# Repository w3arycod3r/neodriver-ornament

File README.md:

# neodriver-ornament
# Demo

# Goal
Create a rechargeable, battery-powered Christmas ornament using Adafruit's ["NeoPixels"](https://www.adafruit.com/category/168) (WS2812B RGB addressable LEDs). The ornament should contain a hole for a ribbon to hang on a tree. The ornament should be "small enough" as to not look out of place on a tree. It should be balanced and as symmetrical as possible so that it will hang straight. The weight should be comparable to other common ornaments. The battery should last for several days/weeks of continuous use.

Animations should be colorful, interesting, and eye-catching. It is acceptable to have a low duty cycle, i.e. the LEDs can have a short ON time playing an animation followed by a longer OFF time to save power. 
# Hardware
For the LEDs, I found various carrier boards of the [WS2812B](docs/WS2812B/WS2812B.pdf) RGB LEDs on eBay. I found square matrices, rings, and circles of various sizes. Search for "WS2812B Ring" or "WS2812B 5X5". Most of these boards simply had the LEDs soldered on one side with appropriate decoupling caps and traces connecting them all in a chain. The important connections (VDD, DIN, & GND) were exposed on the other side, to surface mount pads. I used small stranded wires from ribbon cables to fashion my own cables and connectors for each board. I soldered the wires to the pads, providing some strain relief with hot glue, then crimped a 3P JST-XH female connector to the other end. I would use a male 3P JST-XH on my driver board and connect the LED boards using this interface. This would make it easy to switch out and test different LED boards. Making these connectors was tedious and the solder connections are quite fragile.

I chose the [ATtiny85](https://www.microchip.com/en-us/product/ATTINY85) for the microcontroller, as it is small, inexpensive, has various low-power modes, is available in a DIP-8 package, has sufficient I/O, and has some Arduino IDE support with extensions. I wanted all my components to be through-hole for easy assembly. I planned to have a potentiometer for brightness control, two pushbuttons for changing animations, and a power switch.

Later, I would discover that the NeoPixels drew several milliamps of current, even when they were switched OFF (commanded to show RGB = 0,0,0). So, I picked a nMOS power transistor to switch the GND of the NeoPixels using the microcontroller. I also switched the GND on the pot to save additional power. 

For the battery, I found a neat module which combines a LiFePO4 cell, holder, and USB charge circuit into a single, easy to solder PCB:

https://www.tindie.com/products/silicognition/lifepo4weredusb/  

I wanted to be able to reprogram the microcontroller after the device was assembled, so I included a AVR-ISP header on the board. Not quite as convenient as the USB connector on an Arduino, but good enough for my purposes. This means that I will need a AVR-ISP programmer. I used the official [Atmel-ICE](https://www.microchip.com/en-us/development-tool/ATATMEL-ICE) programmer. I looked into some of the third-party programmers, but I wasn't happy with the way they handled powering the board. The Atmel-ICE does not power the board but instead samples the VDD line and converts the 5V USB programming signals to the voltage level your board uses.

# Schematic

A few notes about the schematic: 
1. I added a jumper in series with the battery positive terminal so I could easily measure power consumption of the entire circuit. This was very useful later during my power optimization efforts.
2. C1 is a decoupling cap for the micro, which will be placed close to the power pins during layout.
3. The micro is at the heart of the circuit, reading the switches and pot inputs, driving the single data line for the NeoPixels, and controlling the nMOS power transistor. Internal pull-ups are used for the switches.
4. R2 is in series with the NeoPixel DIN, based on advice from Adafruit. In theory, this resistor reduces the reflections (sharp over-voltage peaks) on this high-speed digital data line.
5. The I/O lines are shared with the programming lines, with isolation resistors where necessary (R3). There is a pull-up (R1) on the reset line, so that the micro is only reset when the programmer brings the line low.
6. R5 and C3 form a low-pass filter on the analog pot line, to remove any noise which may be on this line. The ADC inside the micro is configured to sample this pin.
7. R4 is a pull-down resistor so that the nMOS is OFF by default. The micro will bring the gate of the nMOS high in order to turn on the transistor and allow the NeoPixels to be powered.
8. There is a bulk cap (C2) close to the NeoPixel connector to buffer the power for the LEDs. These LEDs switch ON and OFF quickly and they require large spikes of current from the power rail. The cap will provide this current while smoothing out the voltage.
9. I picked the IRLU8743PBF for Q1 based on the convenient through-hole package (I-PAK), low ON resistance (~3.1 mOhms), small size, and low threshold voltage (~1.9V). However, it is a bit pricy. Others could certainly work in its place.

# PCB Design
## Breadboard & Protoboard
First, I soldered together a prototype on a piece of protoboard, based on my initial schematic. I also created a breadboard version for easy experimentation.

This wasn't very attractive, and it didn't hang very well on the tree, so I sought out to design a custom PCB. This was my first PCB design, so I learned a lot along the way. I decided to use KiCad, since it is FOSS and very beginner friendly. I watched and followed along with Digi-Key's [YouTube tutorial](https://www.youtube.com/playlist?list=PLEBQazB0HUyR24ckSZ5u05TZHV9khgA1O) on KiCad. Should you want to get a batch of these boards fabbed, you can find the [gerbers](kicad/export/gerbers) in the repo.

## v01
The layout for v01 of the PCB design was heavily based on the protoboard layout, for simplicity. I used [JLCPCB](https://jlcpcb.com/) to get the boards manufactured.  

## v02
For v02, I made several improvements:
1. Use a circular shape for smaller overall footprint and hopefully better balance on the tree
2. Place the battery (heaviest component) for better balance.
3. Replace the straight ISP header with a right angle one so that the port can be accessed even when the LEDs are hot-glued in place.
4. Add the nMOS transistor to switch the NeoPixel GND when in a low-power state.
5. Add a single hole at the top to attach a ribbon for hanging purposes.
6. Add rubber feet on bottom so the board can sit on a table without scratching the table or shorting connections.
7. Add some festive PCB art on the back! :D  

I discovered that the potentiometer was burning some power as well. Since I didn't need to read the value of the pot while in a low-power state, I decided to switch the GND of the pot using the same nMOS for the NeoPixels. I cut the GND connection on the pot and added a bodge wire to fix this, shown below:

## v03
For v03, I made a few minor improvements:
1. Rewire the pot so that the GND is switched along with the NeoPixel GND.
2. Rotate some components 45 degrees so that they are easier to access when the LEDs are fixed on top.
3. Add RC low-pass filter on the analog pot line, to filter out switching noise from NeoPixel data signal.
4. Enlarge pads on battery terminals for better connection

# Software
The main app [neo_driver_app.cpp](microchip-studio/neo_driver_app/neo_driver_app.cpp) has several important functions:
1. Process HMI inputs (left, right switches and potentiometer). The switches can scroll through all the animations and the pot can adjust the brightness of the LEDs.
2. LED adjustment mode: Holding one of the switches will cause the device to enter a LED adjustment mode. In this mode, pressing the left or right switches will decrement or increment the number of LEDs controlled by the device. This allows different sizes of matrices or rings to be used. Holding one of the switches again will save your adjustment into EEPROM memory, so that it is retained between power cycles.
3. Shuffle mode: Play the defined animations in a random sequence, without user intervention. After playing an animation, enter a low-power mode with micro in deep sleep, LEDs and pot OFF. The sleep time is variable, depending on the length of the last played animation. Wakeup from sleep is achieved using the watchdog timer. Also, pressing one of the switches will wake the device as well.
4. Battery management: Monitor for a low battery condition by measuring VDD on the micro and checking it against a set threshold. When this condition occurs, a flashing red "low battery" icon is shown for a few seconds and the device enters the low-power mode without the watchdog timer set. Therefore, the device will remain in low-power mode until it is woken with a switch or a power cycle. If the battery is still low, the device will repeat the "low battery" animation and return to the low-power mode. The device will be "locked out" until the battery voltage rises to a reasonable level (as a result of the user charging the battery).

I wrote the code with modularity in mind, so that it would be easy to add or remove animations. Also most parameters are pulled out into constants or data structures, so they can be easily tweaked.

## Animations
### Scrolling Text
In the EEPROM, I had space for 85 ASCII characters in a 5x5 bitmap font. The top 3 bits of each byte were unused. Most notably, I covered all the digits, capital letters, and some punctuation marks and symbols. In the program memory (flash), I store a few message strings in ASCII. This animation can select one of the messages and scroll it across the matrix in one color or in a flowing "rainbow" color effect.

Rendering a 5x5 framebuffer containing a character onto the 5x5 matrix was tricky because the LEDs are indexed sequentially, in a zig-zag pattern chosen for convenient routing on the matrix PCB. Below is an illustration of the index problem, with my choice for numbering rows and columns:

I came up with the following conversion equations for (row,col) to pixel index, depending on the orientation of the matrix (which determines location of first pixel and the pattern direction):
```C++
// Calculate pixel index from (row,col)
    #if   ANIM_ROT_SEL == 1
        if (u8_col % 2 == 0) { u8_pixIndex = u8_col*5     + 4-u8_row; }
        else                 { u8_pixIndex = u8_col*5     +   u8_row; }
    #elif ANIM_ROT_SEL == 2
        if (u8_row % 2 == 0) { u8_pixIndex = (4-u8_row)*5 + 4-u8_col; }
        else                 { u8_pixIndex = (4-u8_row)*5 +   u8_col; }
    #elif ANIM_ROT_SEL == 3
        if (u8_col % 2 == 0) { u8_pixIndex = (4-u8_col)*5 +   u8_row; }
        else                 { u8_pixIndex = (4-u8_col)*5 + 4-u8_row; }
    #elif ANIM_ROT_SEL == 4
        if (u8_row % 2 == 0) { u8_pixIndex = u8_row*5     +   u8_col; }
        else                 { u8_pixIndex = u8_row*5     + 4-u8_col; }
    #endif
```
### SARS-CoV-2 Blink
For this animation, I was inspired by PaulKlinger's [Virus Blinky](https://github.com/PaulKlinger/freeform-virus-blinky). I created two versions of this animation, one using a "quarter" pattern, suitable for rings, and one using letters, suitable for the 5x5 matrix.

The quarter pattern blinks through the [RNA](https://en.wikipedia.org/wiki/RNA) sequence of the [SARS-CoV-2](https://en.wikipedia.org/wiki/Severe_acute_respiratory_syndrome_coronavirus_2) virus, lighting up one quarter of the LEDs in a specific color corresponding to the current [base](https://en.wikipedia.org/wiki/Nucleobase).
The letter pattern instead blinks the letters corresponding to the base, again with a corresponding color.

The animation blinks a few letters of the sequence, then goes to sleep. When this animation is chosen again, it will retain its place in the sequence and continue from there. Due to space constraints, I was only able to store the first 320 bases of the sequence. This is sufficient to create an interesting, random looking animation.
### Frame Sequences
Since many of the ASCII chars in the range I selected were unused in my message strings, I used these for frames of animation instead. First, I created the animations using [GIMP](https://www.gimp.org/) on my PC. Once I was happy with how they looked, I copied them bit by bit into the font memory. I created a struct in the main program that contains the parameters for each animation. Each animation could be defined as STATIC or SHIFT mode. STATIC is a non-moving animation, fixed in place, stepping through a frame sequence. SHIFT is a moving animation, scrolling in some direction while also stepping through frames.

As an example, below is the (annotated) animation data for the "Pacman" animation.
```C++
// Frame ASCII sequences
const char PROGMEM sz_frames1[] = "gh";     // Pacman  ( 12   : gh  )  -- Which ASCII chars in the char set correspond to the animation frames in memory?

// Frame sequence config data

// Sequence 1 - Pacman
FRAMES_CONFIG_T st_sequence1 = {
    200,                         // uint16_t u16_frameStep_msec;  -- "on" time for each frame in the sequence.
    COLOR_YELLOW,                // uint32_t u32_color;           -- Color. Set to 0 for dynamic effect.
    sz_frames1,                  // uint8_t* pu8_frames;          -- Pointer to the frame sequence array stored in flash.
    FRAMES_MODE_SHIFT,           // uint8_t  u8_mode;             -- Mode of operation. A value from _FRAMES_MODE_T.

    // STATIC params
    0,                           // uint8_t  u8_seqRepeatCnt;     -- Number of times to repeat the frame seq for each anim cycle in STATIC mode.

    // SHIFT params
    2,                           // uint8_t  u8_frameShiftSync;   -- Number of frames between shifts, in SHIFT mode.
    -4,                          // int8_t   i8_startPosX;        -- Init X,Y position. Should start onscreen.
    0,                           // int8_t   i8_startPosY;        -- 
    1,                           // int8_t   i8_shiftStepX;       -- The X shift to perform on each shift step. Can be pos, neg, or zero.
    0                            // int8_t   i8_shiftStepY;       -- The Y shift to perform on each shift step. Can be pos, neg, or zero.
};
```
## Challenges
The biggest challenge was space. The ATtiny85 only has 8KB of code space and 512B of EEPROM. I used EEPROM to store bitmap font data used for the scrolling messages, as well as the SARS-CoV-2 base data for the associated animation. I stored message strings and other animation sequence data in flash. To get all of this to fit, I had to carefully optimize the code for size. I had to trim down the Adafruit NeoPixel library, removing unnecessary features and sizing all of the variables as small as possible. You can see the modifications I made in [neo_pixel_slim.h](microchip-studio/neo_driver_app/libs/neo_pixel_slim.h) and [neo_pixel_slim.cpp](microchip-studio/neo_driver_app/libs/neo_pixel_slim.cpp). Also, I had to avoid some bloated Arduino functions and replace them with direct AVR register manipulations.

I used various commands from the AVR toolchain (see [ard_get_size_info.bat](scripts/ard_get_size_info.bat)) to view the size and disassembly of each portion of my code. This was essential during my size optimization efforts, as it showed me where to focus my attention.

# Compile & Flash
## Environment setup
1. Install PowerShell Core (7+)
1. Run `Set-ExecutionPolicy -ExecutionPolicy Bypass -Scope LocalMachine` in admin pwsh window, to allow scripts from downloaded release zips to run.
1. Install [Microchip Studio](https://www.microchip.com/en-us/tools-resources/develop/microchip-studio) (MS) Version 7.0.2594
1. Open the Atmel [Solution](microchip-studio/neodriver-ornament-ms.atsln) within the IDE

## eep_data_write
Font and animation data is stored in the 512B EEPROM of the ATtiny85. So first, the [eep_data_write.cpp](microchip-studio/neo_driver_app/eep_data_write.cpp) app should be flashed and ran on the hardware. There is a config in MS with the same name which compiles this app via a `#define`.

This app will flash the required data into the EEPROM and verify it. The first NeoPixel flashes green to indicate success, red to indicate verification failure.

## neo_driver_app
The [neo_driver_app.cpp](microchip-studio/neo_driver_app/neo_driver_app.cpp) file is the main program. The "Release" and "Debug" configs in MS will compile this.

## VS Code
1. Compile all 3 configs within MS at least once.
1. Open repo folder within VS Code.
1. Invoke the desired build task within VS Code which will build, flash, and set fuses to required values.

# Useful Links
https://github.com/PaulKlinger/freeform-virus-blinky  
http://batchout.blogspot.com/2018/02/five-by-five-my-5x5-pixel-font.html  
https://www.ebay.com/itm/224246288057

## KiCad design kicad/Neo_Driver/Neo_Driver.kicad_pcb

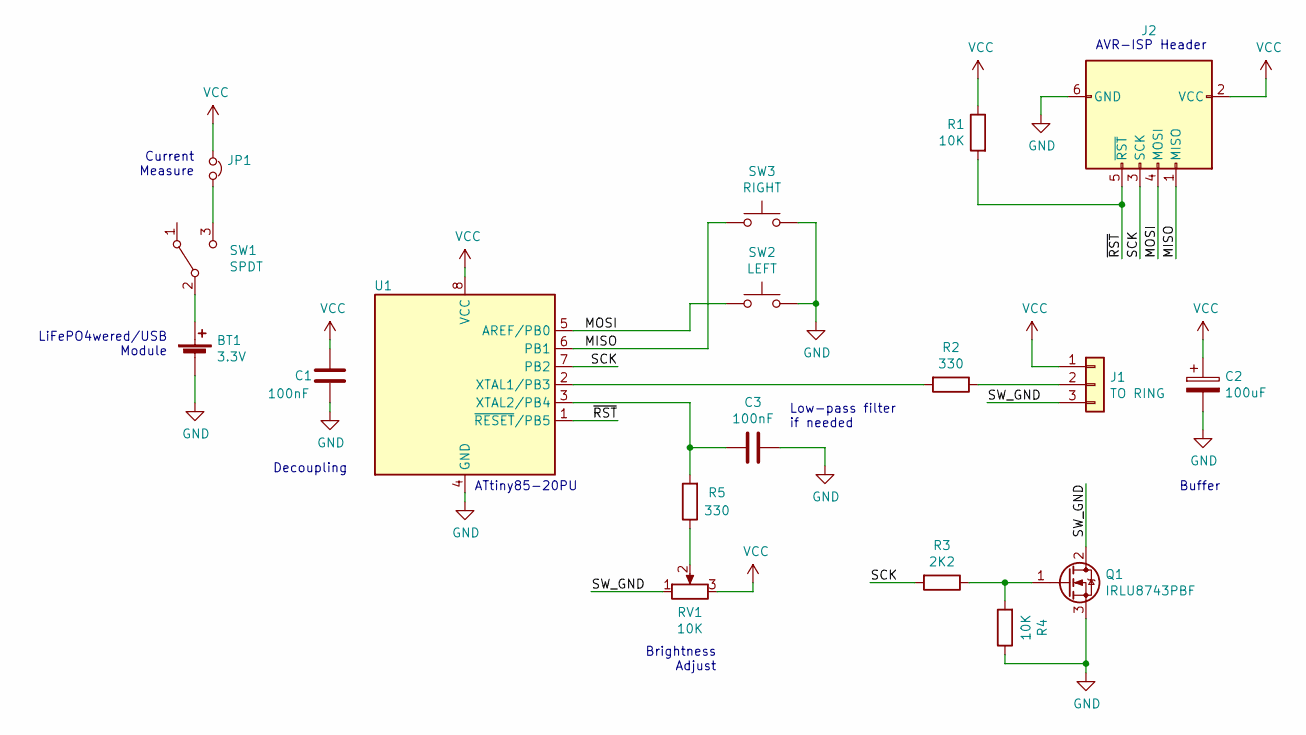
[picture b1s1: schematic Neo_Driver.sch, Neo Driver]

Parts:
BT1: 3.3V; LiFePO4wered_USB_Slim
C1, C3: 100nF; C_Disc_D3.8mm_W2.6mm_P2.50mm
C2: 100uF; CP_Radial_D5.0mm_P2.00mm
J1: TO RING; JST_XH_B3B-XH-A_1x03_P2.50mm_Vertical
J2: ISP; IDC-Header_2x03_P2.54mm_Horizontal
JP1: CURR MEAS; PinHeader_1x02_P2.54mm_Vertical
Q1: IRLU8743PBF; TO-251-3_Vertical
R1, R4: 10K; R_Axial_DIN0207_L6.3mm_D2.5mm_P7.62mm_Horizontal
R2, R5: 330; R_Axial_DIN0207_L6.3mm_D2.5mm_P7.62mm_Horizontal
R3: 2K2; R_Axial_DIN0207_L6.3mm_D2.5mm_P7.62mm_Horizontal
RV1: 10K; Potentiometer_Bourns_3386P_Vertical
SW1: SPDT; SW_Slide_SPDT_8.6x3.7mm_P2.50mm
SW2: LEFT; SW_PUSH_6mm_H5mm
SW3: RIGHT; SW_PUSH_6mm_H5mm
U1: ATtiny85; DIP-8_W7.62mm_Socket

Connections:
/MISO: J2.1 (MISO), SW3.1, U1.6 (PB1)
/MOSI: J2.4 (MOSI), SW2.1, U1.5 (AREF/PB0)
/SCK: J2.3 (SCK), R3.2, U1.7 (PB2)
/SW_GND: J1.3, Q1.2 (D), RV1.1
/~RST: J2.5 (~RST), R1.2, U1.1 (~RESET~/PB5)
GND: BT1.2 (-), C1.2, C2.2, C3.1, J2.6 (GND), Q1.3 (S), R4.1, SW2.2, SW3.2, U1.4 (GND)
unnamed: BT1.1 (+), SW1.2 (B)
unnamed: C3.2, R5.2, U1.3 (XTAL2/PB4)
unnamed: J1.2, R2.1
unnamed: JP1.2, SW1.3 (C)
unnamed: Q1.1 (G), R3.1, R4.2
unnamed: R2.2, U1.2 (XTAL1/PB3)
unnamed: R5.1, RV1.2
VCC: C1.1, C2.1, J1.1, J2.2 (VCC), JP1.1, R1.1, RV1.3, U1.8 (VCC)

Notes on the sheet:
Decoupling
Buffer
Low-pass filter if needed
LiFePO4wered/USB Module
Brightness Adjust
Current Measure
ATtiny85-20PU
AVR-ISP Header

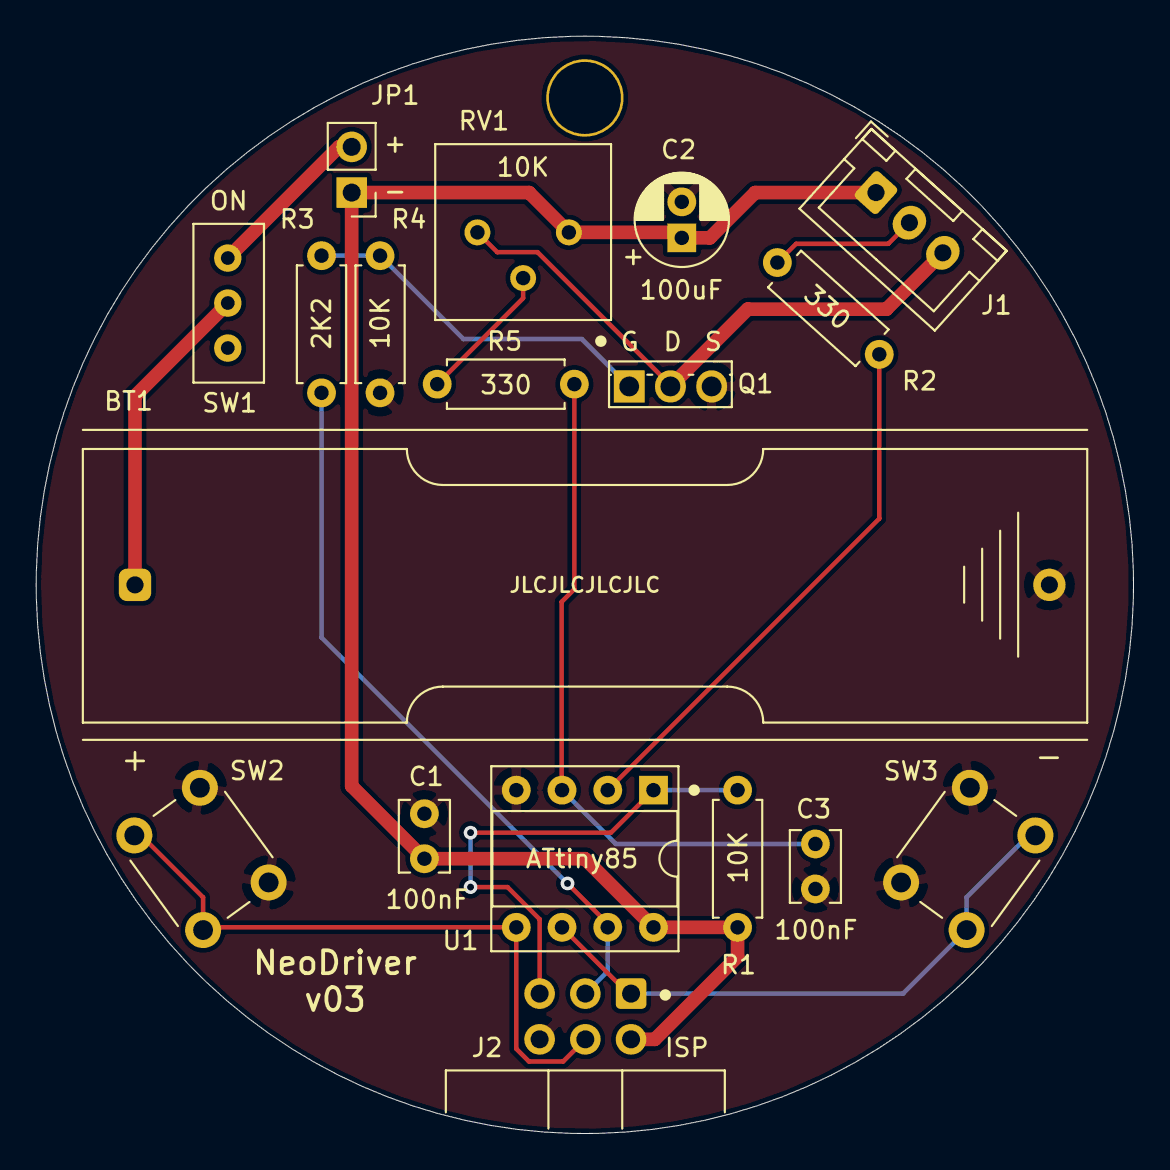
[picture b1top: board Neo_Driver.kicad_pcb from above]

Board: 2 copper layers, 61.0 x 61.0 mm, 18 parts (0 on the bottom side), 14 nets.

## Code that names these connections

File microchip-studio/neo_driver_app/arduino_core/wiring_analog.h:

/* File:      wiring_analog.h
 * Author:    Garrett Carter
 * Purpose:   Analog I/O functions
 */

#ifndef WIRING_ANALOG_H
#define WIRING_ANALOG_H

#include <Arduino.h>
#include <stdbool.h>
#include <utility.h>

#ifdef __cplusplus
extern "C" {
#endif

/****************************** DEFINES ******************************/
// These prescaler bits correspond to "divide by 64"
//----> 8 MHz (Sys Clk) / 64 = 125 KHz (ADC Clk)
#define ADC_CLK_PRESCALER   (0b110)

#define ADC_NUM_BITS            (10)
#define ADC_MAX_VALUE           ((1 << ADC_NUM_BITS) - 1)
#define MILLIVOLTS_PER_VOLT     (1000)
#define ADC_INT_1V1_REF_VOLTAGE (1.1)

// Below defines are the possible values for the ADMUX_REFS bits in the ADMUX register.
#define ADMUX_REFS1_REFS0_MASK           (0b011)
#define ADMUX_REFS2_MASK                 (0b100)
// VCC used as Voltage Reference, disconnected from PB0 (AREF).
#define ADMUX_REFS_VCC_AS_REF            (0b000)
// External Voltage Reference at PB0 (AREF) pin, Internal Voltage Reference turned off.
#define ADMUX_REFS_EXT_PB0_AREF          (0b001)
// Internal 1.1V Voltage Reference.
#define ADMUX_REFS_INT_1V1_REF           (0b010)
// Internal 2.56V Voltage Reference without external bypass capacitor, disconnected from PB0 (AREF).
// The device requires a supply voltage of 3V in order to generate 2.56V reference voltage.
#define ADMUX_REFS_INT_2V56_NO_BYP_CAP   (0b110)
// Internal 2.56V Voltage Reference with external bypass capacitor at PB0 (AREF) pin.
// The device requires a supply voltage of 3V in order to generate 2.56V reference voltage.
#define ADMUX_REFS_INT_2V56_WITH_BYP_CAP (0b111)

//                  ATMEL ATTINY85
//
//                      +-\/-+
//  ADC0  !RESET  PB5  1|    |8  VCC
//  ADC3  PCINT3  PB3  2|    |7  PB2  PCINT2  ADC1
//  ADC2          PB4  3|    |6  PB1  PCINT1     
//                GND  4|    |5  PB0  PCINT0  AREF
//                      +----+
// Below defines are the possible values for the MUX bits in the ADMUX register.
// "SE" stands for Single Ended.
#define ADMUX_MUX_MASK          (0x0f)

#define ADMUX_MUX_SE_ADC0_PB5     (0b0000)
#define ADMUX_MUX_SE_ADC1_PB2     (0b0001)
#define ADMUX_MUX_SE_ADC2_PB4     (0b0010)
#define ADMUX_MUX_SE_ADC3_PB3     (0b0011)
// 0b0100 - 0b1011 are used for differential channels.
#define ADMUX_MUX_SE_VBG_INT_1V1  (0b1100)  // Internal bandgap (1.1V) voltage reference
#define ADMUX_MUX_SE_GND          (0b1101)
#define ADMUX_MUX_SE_ADC4         (0b1111)  // Temperature sensor, must be used with 1.1V internal reference.

// This macro computes the ADMUX register value based on the channel and reference selection bits, at compile time.
// This assumes ADLAR is always 0.
#define COMPOSE_ADMUX(ch, ref) (((ref & ADMUX_REFS1_REFS0_MASK) << REFS0) | (((ref & ADMUX_REFS2_MASK) >> 2) << REFS2) | ((ch & ADMUX_MUX_MASK) << MUX0))

// Analog channel and reference for VCC measurement
#define VCC_AN_MEAS_CH   (ADMUX_MUX_SE_VBG_INT_1V1)
#define VCC_AN_MEAS_REF  (ADMUX_REFS_VCC_AS_REF)

/****************************** PROTOTYPES ******************************/
void adc_init();
uint16_t adc_read(uint8_t ch, uint8_t analog_reference);

#ifdef __cplusplus
} // extern "C"
#endif

#endif /* WIRING_ANALOG_H */

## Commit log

2021-12-10 init push
2021-12-10 remove build files
2021-12-11 img update
2021-12-11 crop img
2021-12-12 add gifs
2021-12-12 update img
2021-12-12 rename
2021-12-12 sprites
2021-12-12 add credit
2021-12-12 spellcheck
2021-12-13 downscale images
2021-12-18 add credit and image
2021-12-18 Create LICENSE
2021-12-31 Tweaked low battery behavior
2022-01-01 Brightness debug
2022-09-07 Initial support for pumpkin animation
2022-09-10 Revert "Initial support for pumpkin animation"
    This reverts commit 972e4e4ec1676475467f81d9df17f1b82537a973.
    Halloween changes will be developed in the halloween-additions branch.
    Leave the change to vscode settings
2022-09-10 Add candle flicker anim Started blink pattern anim
2023-12-22 Kenny's customizations
2023-12-23 Cassidy's customizations
2024-01-16 vscode fix for annoying popup :/
2024-01-16 Move some EEPROM definitions out into a library included by both sketches
2024-01-16 - rework build scripts - Remove extra Sequence data - Add conditional compile option for cov sequence data - move ard_utility - Make define names more detailed
2024-01-17 eeprom work - tweak build scripts - add compression and extraction routines - rework common defines
2024-01-18 Correct the line extraction function
2024-01-18 char set tweaking - remove padding in front - add a few new frames - add in Lost numbers message from cassidy's branch
2024-01-18 update init param
2024-01-19 Fix lib reference
2024-01-19 Optimize eeprom usage (#1)
    * vscode fix for annoying popup :/
    * Move some EEPROM definitions out into a library included by both sketches
    * - rework build scripts
    - Remove extra Sequence data
    - Add conditional compile option for cov sequence data
    - move ard_utility
2024-01-19 Initial relocation Needs more work... Code overflows Flash space by 414 bytes!
2024-01-20 Remove some unused libraries, replace adafruit neopixel library with the slim version. Refactor the EEP program to use the slim neopixel library
2024-01-20 Remove some more unused parts of the arduino core
2024-01-20 Fully move neo pixel slim
2024-01-21 compilation fixes -- Enable link time optimization (LTO)
2024-01-21 Combine into a single project
2024-01-21 Fix configs
2024-01-21 Remove more unused arduino stuff -- avoid __vector_1 in symbols!
2024-01-21 cleanup
2024-01-22 Create separate build config for eep_data_write Rework scripts to use AS Makefile and programmer CLI
2024-01-22 fix paths
2024-02-10 microchip studio debugger cannot do debugging if LTO is turned on. Release config will use link time optimization, debug config will not.
2024-02-11 Add automatic disabling of debugwire, updating of fuses during flash. This makes it easier to switch between debugging and release versions
2024-02-11 fix config
2024-02-11 Initial relocation (#2)
    * Initial relocation
    Needs more work...
    Code overflows Flash space by 414 bytes!
    * Remove some unused libraries, replace adafruit neopixel library with the slim version. Refactor the EEP program to use the slim neopixel library
    * Remove some more unused parts of the arduino core
    * Fully move neo pixel slim
2024-02-11 Make flashing scripts more robust
2024-02-11 Make flashing scripts more robust (#3)
2024-02-16 change arduino setup to microchip studio setup
2024-02-16 replace back slashes with forward slashes
2024-02-16 replace arduino setup instructions with microchip studio (#4)
    * change arduino setup to microchip studio setup
    * replace back slashes with forward slashes
2024-04-27 remove old arduino scripts
2024-04-27 start converting scripts to pwsh
2024-04-27 complete ms-update-fuses.ps1 conversion
2024-04-27 add param and robustness
2024-04-28 Break apart and convert scripts
2024-04-28 remove converted scripts
2024-04-28 Convert development sequence and update VS code tasks
2024-04-28 add release scripts
2024-04-28 add release task
2024-04-28 add ii
2024-04-28 change exec policy
2024-07-15 work on stats add to eeprom map add logic for counters -- Updating and resetting Remove unused double click code
2024-07-15 move reference code work on binary to decimal anim function need to continue with string reversal
2024-07-18 Add utility functions, remove pixel count adjustment we are fairly fixed on the 5x5 matrix hardware.
2024-08-07 reorganize code
2024-08-07 Work on size info script
2024-08-08 work on size info
2024-08-08 add memory usage totals and percentage
2024-08-10 make stuff static, a rec from atmel on downsizing; rework task structure
2024-08-10 add a friendly script for releases
2024-08-10 Move progmem arrays from .h file to .cpp file to avoid double allocation in flash
2024-08-10 Static function prototypes make no sense in .h files...
2024-08-10 remove some unneeded arduino code.
2024-08-10 More clean up and pruning of the Arduino code
2024-08-10 update vscode config
2024-08-11 replace stdlib random with my own prng implementation
2024-08-11 remove left shift version
2024-08-11 add comment
2024-08-11 check voltage script
2024-08-11 replace memset
2024-08-12 update tasks
2024-08-12 task cleanup
2024-08-12 fix typo
2024-08-12 add shortcut
2024-08-15 convert neopixel from CPP to C library; remove dynamic length functionality
2024-08-15 add comment for incoming code
2024-08-15 port over light_ws2812 code; replace adafruit "show" code
2024-08-19 change warning to error
2024-08-19 fix reversed def of maskhi and masklo -- WARNING: LEDs are now showing as all white, max brightness
2024-08-19 add comments
2024-08-19 correct nop calculation; np_show is now working well!!
2024-08-22 code cleanup
2024-08-27 rename delay funcs
2024-08-27 clean up read_vcc_mv
2024-08-27 work on random prng seeding at startup -- Currently the soft reset is not working, the device is locking up after the soft reset.
2024-08-27 add DEBUG_SOFT_RESET_ON_INTERVAL_EN; soft reset functionality; cleanup init routine
2024-09-01 reorg code
2024-09-01 reorg code; move to Atmel's eeprom library
2024-09-02 fix the char drawing bug (it was only setting the first pixel)
2024-09-02 clean up repo -- docs are in the google drive folder
2024-09-02 rename func
2024-09-02 move blocking animations
2024-09-03 reorg code; move non-blocking anims into anim.c
2024-09-03 test prng seeding at startup using "random" adc read
2024-09-03 add note
2024-09-09 move remaining cpp files to c
2024-09-09 Remake atmel studio project from scratch as a C project
2024-09-11 refresh project file
2024-09-11 test debugging
2024-09-11 enable warnings and resolve them
2024-09-11 rework flashing logic to be more efficient
2024-09-11 add time based recovery

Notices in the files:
kicad/Neo_Driver/Neo_Driver.kicad_pcb:
License: CC BY 4.0
kicad/Neo_Driver/Neo_Driver.sch:
creativecommons.org/licenses/by/4.0
